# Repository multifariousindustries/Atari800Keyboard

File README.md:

# Atari 800 Keyboard

Despite using a variety of keyboard manufacturers and designs over its production, it seems that all Atari 800 computers have a keyboard that is destined to fail, if it hasn't already. Luckily, we live in a time where making completely custom keyboards is a hobby, so I figured I could take advantage of this to create a brand new, drop-in replacement keyboard using commonly available parts. 

## Goals

- Drop-in replacement with no modding of the Atari necessary
- Use widely available Cherry MX style switches, so others can choose the feel they prefer.
- Reuse original key caps to keep the original look

# Making your own

## Parts Needed
- 1 PCB 
- 57 Cherry MX style PCB mount switches
- 18 pin right angle header
- 18 Female-Female jumper wires
- 3d printed parts (see Keys and Mounting below)

## PCB

The KiCad files are in the [PCB](/PCB) folder. Also included is a [.zip](/PCB/Atari800Keyboard.zip) file you can upload to your favorite board house for manufacturing. It's a 2 layer design with some vias connecting the sides, so making the PCB at home might be a challenge. 

Assembly is straight forward. Each switch location is labeled for what key it is. Insert PCB mount switches, solder the pins and solder on righit angle pin headers on the bottom for the connection to the Atari. 

I was unable to find 18 pin ribbon cables with single row connectors, so I opted to use a strip of female to female jumper wires. You could also use half of the connections of an IDE cable. 

## Adding Keys

I wanted to use the original key caps from the Atari, as they have special legends and sizes that would be hard to recreate in a modern cap. This required designing a 3D printable adapter to connect the Hi-tek/Stackpole caps to a Cherry MX stem. This adds significant height to the keys, but luckily the original PCB (and therefore the replacement) sit very low in the case and the height of the adapters allow the keys to sit at the same height as the OEM keyboard. The adapters are simply pressed onto the Cherry MX stems and then the Atari caps are pressed into the other side. Friction keeps everything in place. 

### Stackpole Caps

The PCB was designed with the same switch locations as the Stackpole keyboard, so you just need to print 57 of the [standard adapters](/STL/StackpoleMXAdapterV3.1.stl). These are very small and you should be able to print them all at once on most printers. They should be printed with the MX + side facing up and supports are not needed. 

### Hi-Tek Caps

The Hi-tek board I have used caps with offset posts for the larger keys such as the shift and enter keys. Since I only had a stackpole keyboard when designing the PCB, I created special adapter for the 1.5 unit and 2 unit wide keycaps. You'll need to print four of the [1.5u adapters](/STL/StackpoleMXAdapter-1.5U.stl), one [2u adapter](/STL/StackpoleMXAdapter-2U.stl), and 52 of the [standard adapters](/STL/StackpoleMXAdapterV3.1.stl). Both the wide and standard adapters should be printed with the MX + side facing up and supports are not needed. 

## Mounting the Keyboard

Print two of the [bottom mounts](/STL/BottomMount.stl), and one of each of the top [left](/STL/TopLeftMount.stl), [center](/STL/TopCenterSupport.stl), and [right](/STL/TopRightMount.stl) mounts. The two bottom mounts slide over the bottom edge of the PCB and line up with the mounting holes to ensure the PCB sits at the correct hight, relative to the case. The three top mount pieces are also used for aligning the board, but also serve to support the top of the board and keep it from flexing during use.

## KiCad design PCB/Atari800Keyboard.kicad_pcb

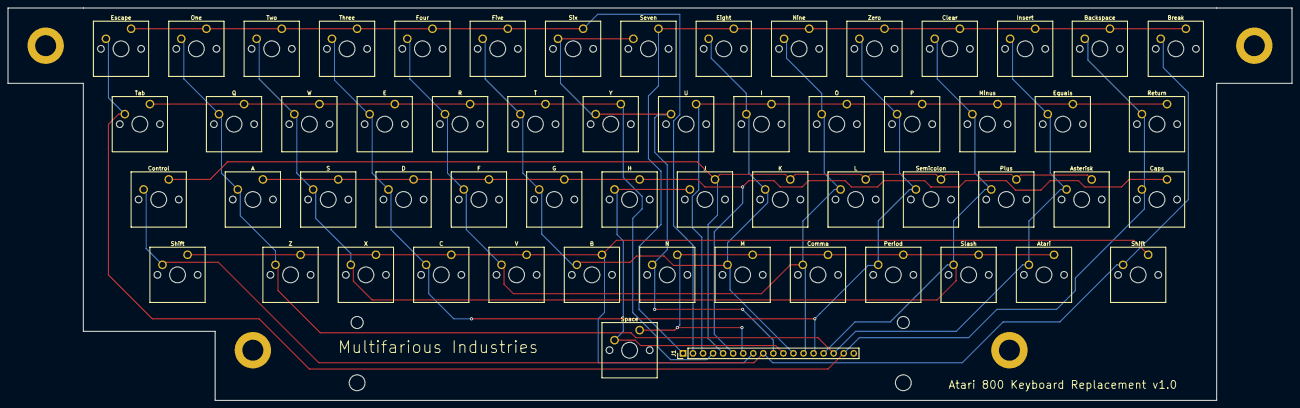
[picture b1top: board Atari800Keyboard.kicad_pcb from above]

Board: 2 copper layers, 324.6 x 99.2 mm, 58 parts (0 on the bottom side), 17 nets.

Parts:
A: KEYSW; SW_Cherry_MX_1.00u_PCB
Asterisk: KEYSW; SW_Cherry_MX_1.00u_PCB
Atari: KEYSW; SW_Cherry_MX_1.00u_PCB
B: KEYSW; SW_Cherry_MX_1.00u_PCB
Backspace: KEYSW; SW_Cherry_MX_1.00u_PCB
Break: KEYSW; SW_Cherry_MX_1.00u_PCB
C: KEYSW; SW_Cherry_MX_1.00u_PCB
Caps: KEYSW; SW_Cherry_MX_1.00u_PCB
Clear: KEYSW; SW_Cherry_MX_1.00u_PCB
Comma: KEYSW; SW_Cherry_MX_1.00u_PCB
Control: KEYSW; SW_Cherry_MX_1.50u_PCB
D: KEYSW; SW_Cherry_MX_1.00u_PCB
E: KEYSW; SW_Cherry_MX_1.00u_PCB
Eight: KEYSW; SW_Cherry_MX_1.00u_PCB
Equals: KEYSW; SW_Cherry_MX_1.00u_PCB
Escape: KEYSW; SW_Cherry_MX_1.00u_PCB
F: KEYSW; SW_Cherry_MX_1.00u_PCB
Five: KEYSW; SW_Cherry_MX_1.00u_PCB
Four: KEYSW; SW_Cherry_MX_1.00u_PCB
G: KEYSW; SW_Cherry_MX_1.00u_PCB
H: KEYSW; SW_Cherry_MX_1.00u_PCB
I: KEYSW; SW_Cherry_MX_1.00u_PCB
Insert: KEYSW; SW_Cherry_MX_1.00u_PCB
J: KEYSW; SW_Cherry_MX_1.00u_PCB
J1: Conn_01x18_Male; PinHeader_1x18_P2.54mm_Vertical
K: KEYSW; SW_Cherry_MX_1.00u_PCB
L: KEYSW; SW_Cherry_MX_1.00u_PCB
M: KEYSW; SW_Cherry_MX_1.00u_PCB
Minus: KEYSW; SW_Cherry_MX_1.00u_PCB
N: KEYSW; SW_Cherry_MX_1.00u_PCB
Nine: KEYSW; SW_Cherry_MX_1.00u_PCB
O: KEYSW; SW_Cherry_MX_1.00u_PCB
One: KEYSW; SW_Cherry_MX_1.00u_PCB
P: KEYSW; SW_Cherry_MX_1.00u_PCB
Period: KEYSW; SW_Cherry_MX_1.00u_PCB
Plus: KEYSW; SW_Cherry_MX_1.00u_PCB
Q: KEYSW; SW_Cherry_MX_1.00u_PCB
R: KEYSW; SW_Cherry_MX_1.00u_PCB
Return: KEYSW; SW_Cherry_MX_1.50u_PCB
S: KEYSW; SW_Cherry_MX_1.00u_PCB
Semicolon: KEYSW; SW_Cherry_MX_1.00u_PCB
Seven: KEYSW; SW_Cherry_MX_1.00u_PCB
Shift: KEYSW; SW_Cherry_MX_2.00u_PCB
Shift#2: KEYSW; SW_Cherry_MX_1.50u_PCB
Six: KEYSW; SW_Cherry_MX_1.00u_PCB
Slash: KEYSW; SW_Cherry_MX_1.00u_PCB
Space: KEYSW; SW_Cherry_MX_6.25u_PCB
T: KEYSW; SW_Cherry_MX_1.00u_PCB
Tab: KEYSW; SW_Cherry_MX_1.50u_PCB
Three: KEYSW; SW_Cherry_MX_1.00u_PCB
Two: KEYSW; SW_Cherry_MX_1.00u_PCB
U: KEYSW; SW_Cherry_MX_1.00u_PCB
V: KEYSW; SW_Cherry_MX_1.00u_PCB
W: KEYSW; SW_Cherry_MX_1.00u_PCB
X: KEYSW; SW_Cherry_MX_1.00u_PCB
Y: KEYSW; SW_Cherry_MX_1.00u_PCB
Z: KEYSW; SW_Cherry_MX_1.00u_PCB
Zero: KEYSW; SW_Cherry_MX_1.00u_PCB

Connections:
/Pin1: Backspace.1, Break.1, Clear.1, Eight.1, Insert.1, J1.1, Nine.1, Seven.1, Zero.1
/Pin2: Escape.1, Five.1, Four.1, J1.2, One.1, Six.1, Three.1, Two.1
/Pin3: Equals.1, I.1, J1.3, Minus.1, O.1, P.1, Return.1, U.1
/Pin4: E.1, J1.4, Q.1, R.1, T.1, Tab.1, W.1, Y.1
/Pin5: Asterisk.1, Control.1, J.1, J1.5, K.1, L.1, Plus.1, Semicolon.1
/Pin6: A.1, Caps.1, D.1, F.1, G.1, H.1, J1.6, S.1
/Pin7: Atari.1, Comma.1, J1.7, M.1, N.1, Period.1, Slash.1, Space.1
/Pin8: B.1, C.1, J1.8, Shift.1, Shift#2.1, V.1, X.1, Z.1
/Pin9: Break.2, Control.2, J1.9, Shift.2, Shift#2.2
/Pin10: J1.10, N.2, Seven.2, Six.2, U.2, Y.2
/Pin11: H.2, J.2, J1.11, Space.2
/Pin12: B.2, Eight.2, Five.2, G.2, I.2, J1.12, K.2, M.2, T.2
/Pin13: Comma.2, F.2, Four.2, J1.13, L.2, Nine.2, O.2, R.2, V.2
/Pin14: C.2, D.2, E.2, J1.14, P.2, Period.2, Semicolon.2, Three.2, Zero.2
/Pin15: Clear.2, J1.15, Minus.2, Plus.2, S.2, Slash.2, Two.2, W.2, X.2
/Pin16: A.2, Asterisk.2, Atari.2, Equals.2, Insert.2, J1.16, One.2, Q.2, Z.2
/Pin17: Backspace.2, Caps.2, Escape.2, J1.17, Return.2, Tab.2

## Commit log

2021-03-08 V1 complete
2021-03-08 Add image to readme
2021-03-10 Create license
